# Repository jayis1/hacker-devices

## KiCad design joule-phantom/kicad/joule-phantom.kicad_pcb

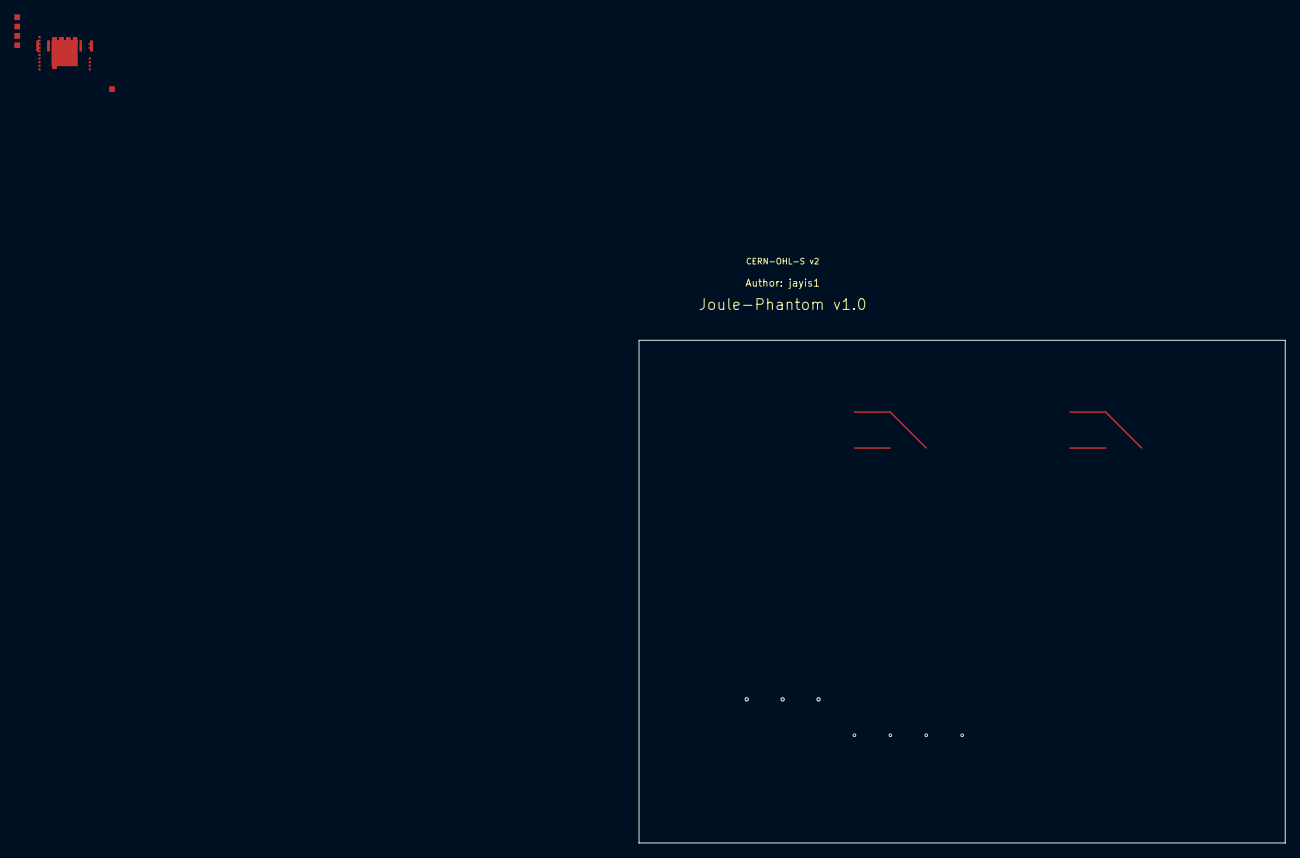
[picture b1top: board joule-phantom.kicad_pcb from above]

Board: 4 copper layers, 90.0 x 70.0 mm, 16 parts (0 on the bottom side), 12 nets.

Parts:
C1, C2: 100nF; C_0402_1005Metric
C3: 10uF; C_0603_1608Metric
D1: Blue; LED_0603_1608Metric
J1: Host_SMBus_6pin; TE_84953-6
J2: Batt_SMBus_6pin; TE_84953-6
R1, R2, R3, R4: 10k; R_0402_1005Metric
R5: 470; R_0402_1005Metric
U1: STM32L432KCU6; QFN-32-1EP_5x5mm_P0.5mm_EP3.65x3.65mm
U2: ESP32-C3-MINI-1
U3, U4: TXS0102DCT; SOT-23-8
Y1: 32.768kHz; Crystal_SMD_3215-2Pin_3.2x1.5mm

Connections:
3V3: C1.1, C2.1, C3.1, R1.1, R2.1, R3.1, R4.1, U1.1, U1.29, U2.1, U2.2, U3.1, U4.1
BATT_PRSNT#: J1.6, J2.6, U1.2
GND: C1.2, C2.2, C3.2, D1.1, J1.4, J2.4, R5.2, U1.10, U1.30, U1.33, U2.15, U3.4, U4.4
LED_DRIVE: D1.2, R5.1, U1.23
SMBALERT#: J1.5, J2.5, U1.3
SMB_CLK_BATT: J2.2, R3.2, U1.21, U4.2
SMB_CLK_HOST: J1.2, R1.2, U1.8, U3.2
SMB_DAT_BATT: J2.3, R4.2, U1.22, U4.3
SMB_DAT_HOST: J1.3, R2.2, U1.9, U3.3
UART_RX: U1.5, U2.3
UART_TX: U1.4, U2.4
VBAT+: J1.1, J2.1, U3.8, U4.8

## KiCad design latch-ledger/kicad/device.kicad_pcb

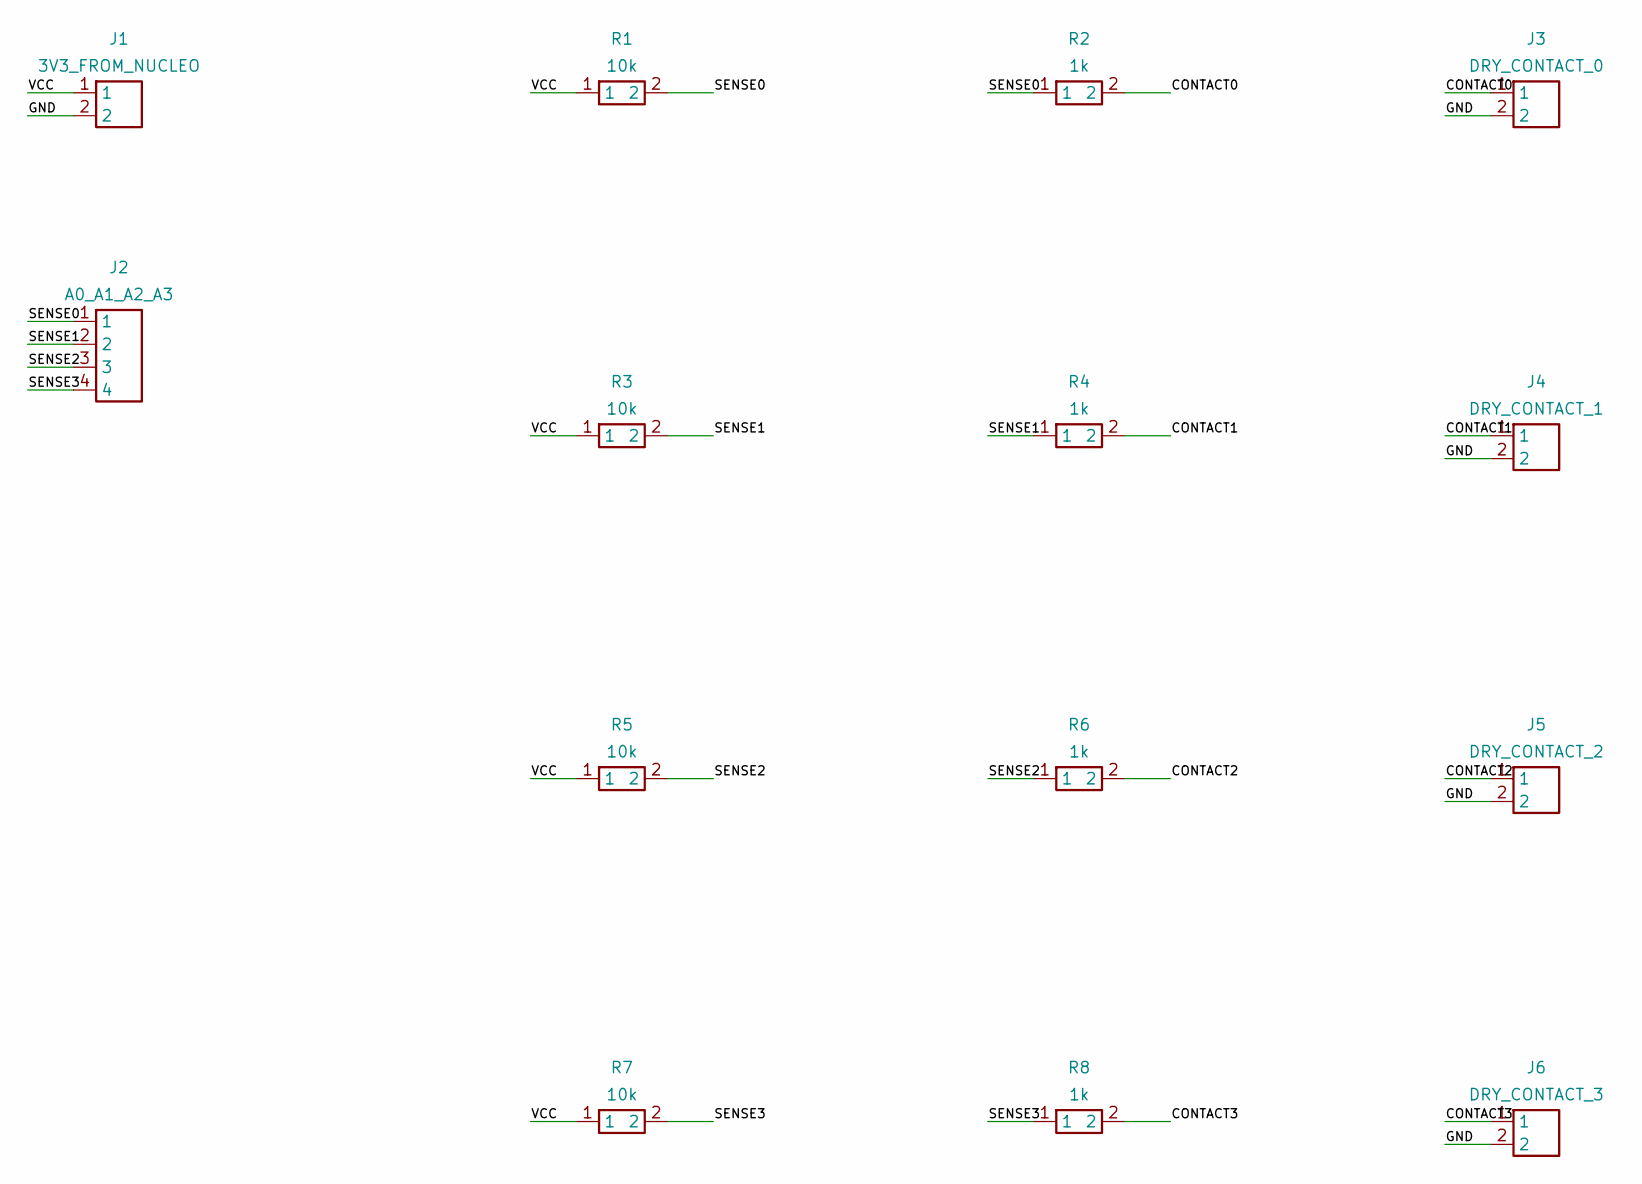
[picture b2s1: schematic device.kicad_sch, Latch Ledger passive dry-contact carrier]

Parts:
J1: 3V3_FROM_NUCLEO; PinHeader_1x02_P2.54mm_Vertical
J2: A0_A1_A2_A3; PinHeader_1x04_P2.54mm_Vertical
J3: DRY_CONTACT_0; PinHeader_1x02_P2.54mm_Vertical
J4: DRY_CONTACT_1; PinHeader_1x02_P2.54mm_Vertical
J5: DRY_CONTACT_2; PinHeader_1x02_P2.54mm_Vertical
J6: DRY_CONTACT_3; PinHeader_1x02_P2.54mm_Vertical
R1, R3, R5, R7: 10k; R_Axial_DIN0207_L6.3mm_D2.5mm_P7.62mm_Horizontal
R2, R4, R6, R8: 1k; R_Axial_DIN0207_L6.3mm_D2.5mm_P7.62mm_Horizontal

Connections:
CONTACT0: J3.1, R2.2
CONTACT1: J4.1, R4.2
CONTACT2: J5.1, R6.2
CONTACT3: J6.1, R8.2
GND: J1.2, J3.2, J4.2, J5.2, J6.2
SENSE0: J2.1, R1.2, R2.1
SENSE1: J2.2, R3.2, R4.1
SENSE2: J2.3, R5.2, R6.1
SENSE3: J2.4, R7.2, R8.1
VCC: J1.1, R1.1, R3.1, R5.1, R7.1

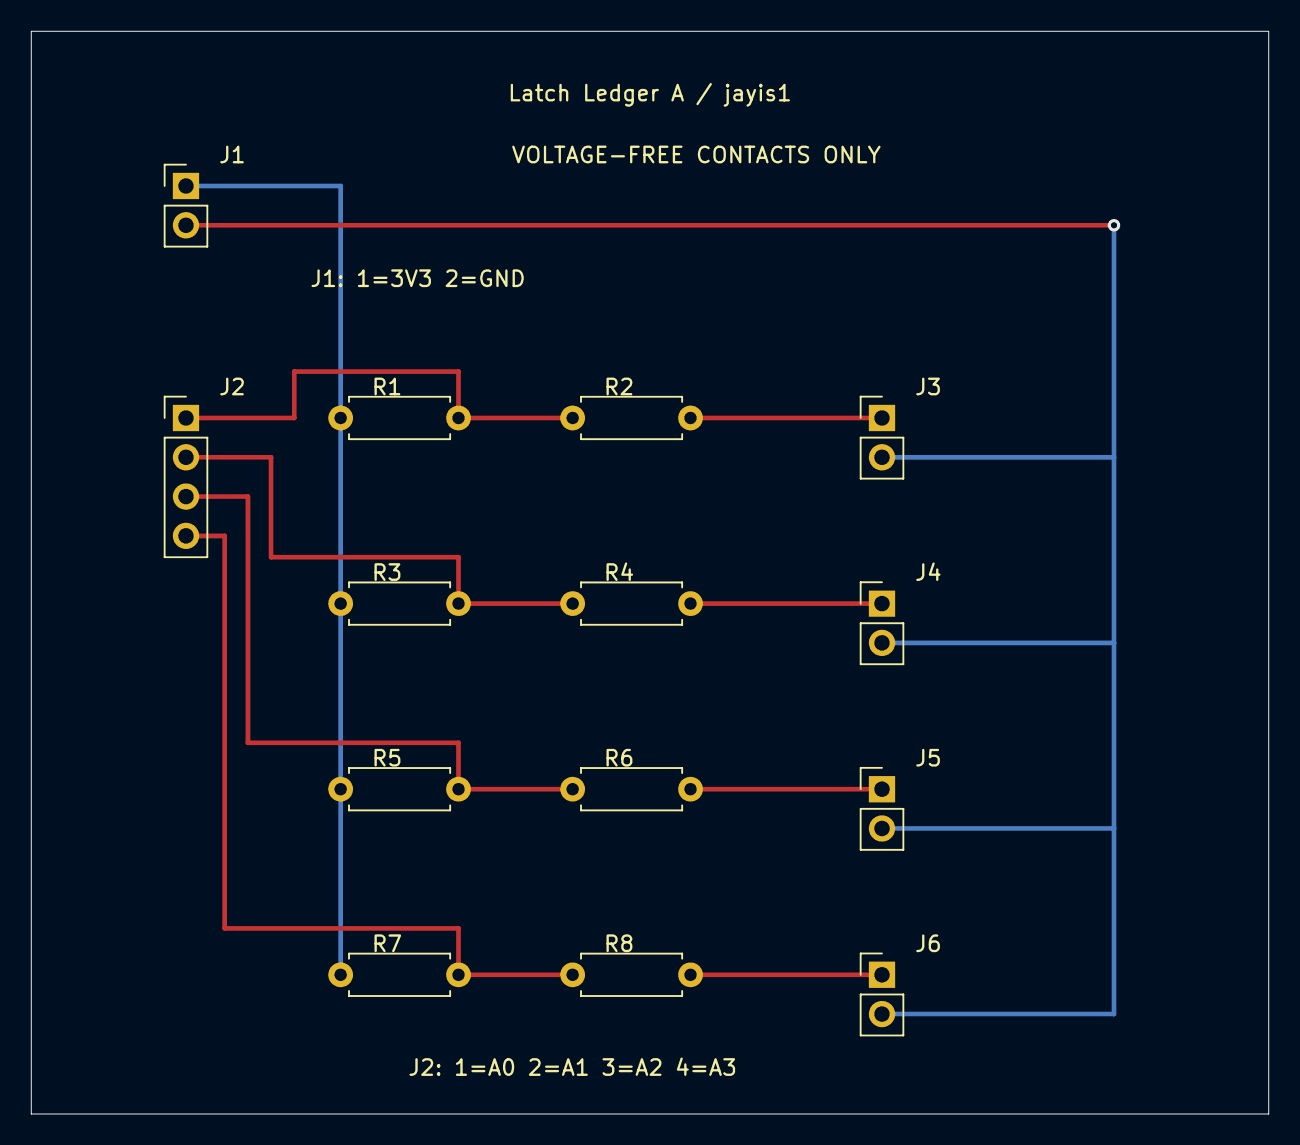
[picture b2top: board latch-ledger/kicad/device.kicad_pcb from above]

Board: 2 copper layers, 80.0 x 70.0 mm, 14 parts (0 on the bottom side), 10 nets.

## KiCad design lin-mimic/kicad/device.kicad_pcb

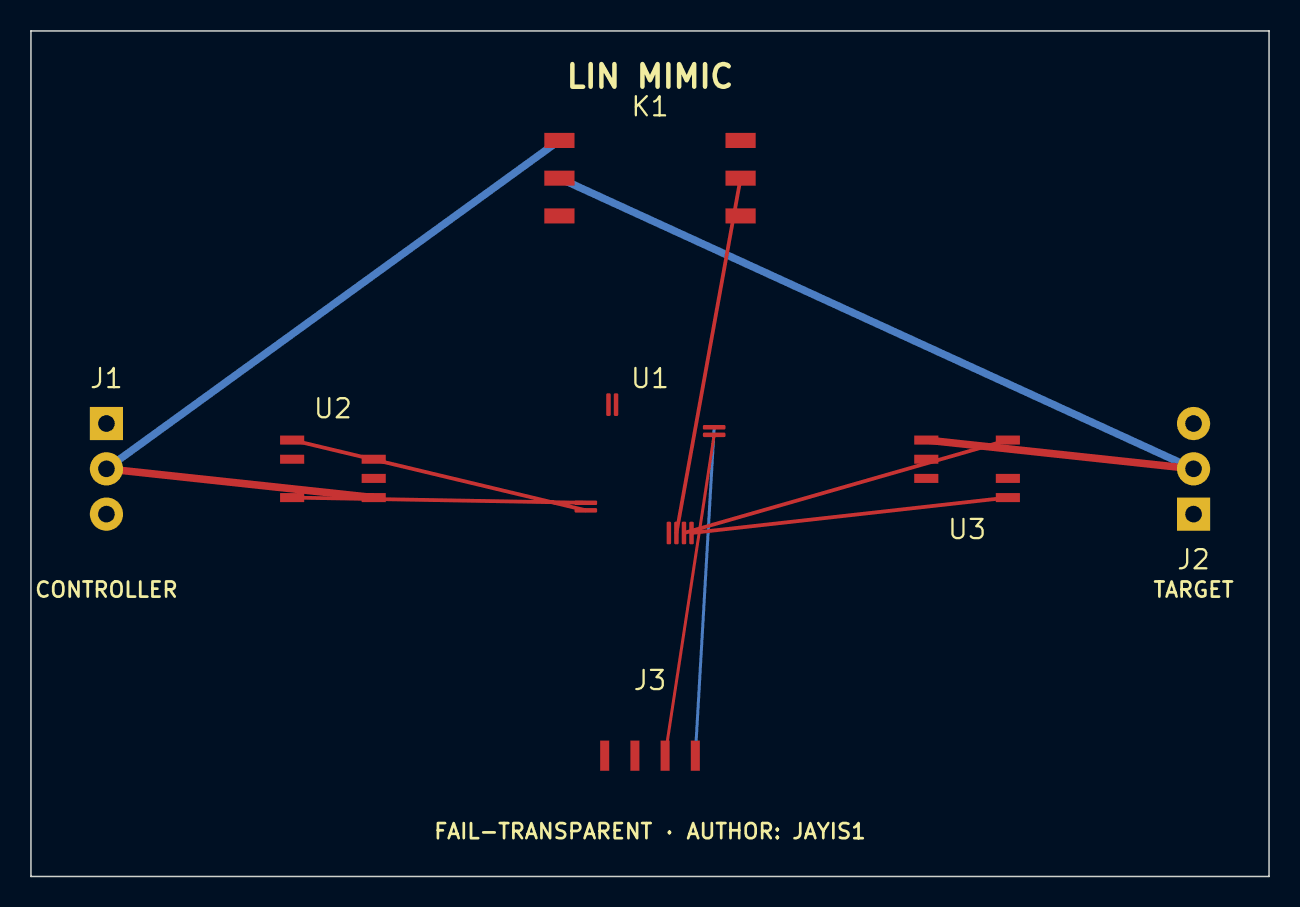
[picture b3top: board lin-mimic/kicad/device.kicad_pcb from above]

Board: 4 copper layers, 82.0 x 56.0 mm, 7 parts (0 on the bottom side), 12 nets.

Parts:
J1: CONTROLLER; Molex_Micro-Fit_3.0_43650-0300_1x03_P3.00mm_Horizontal
J2: TARGET; Molex_Micro-Fit_3.0_43650-0300_1x03_P3.00mm_Horizontal
J3: USB-C; USB_C_Receptacle_GCT_USB4105-xx-A_16P_TopMnt_Horizontal
K1: TQ2SA-L2-5V; Relay_DPDT_Panasonic_TQ2SA
U1: STM32G474CBT6; LQFP-48_7x7mm_P0.5mm
U2: TJA1021 CONTROLLER; SOIC-8_3.9x4.9mm_P1.27mm
U3: TJA1021 TARGET; SOIC-8_3.9x4.9mm_P1.27mm

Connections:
+3V3: U1.48, U2.8, U3.8
GND: J1.3, J2.3, J3.A1, K1.3, K1.4, U1.24, U1.47, U2.2, U3.2
LIN_CONTROLLER: J1.2, K1.1, U2.6
LIN_TARGET: J2.2, K1.2, U3.6
RELAY_DRIVE: K1.5, U1.23
USART2_RX: U1.13, U2.4
USART2_TX: U1.12, U2.1
USART3_RX: U1.22, U3.4
USART3_TX: U1.21, U3.1
USB_DM: J3.A7, U1.36
USB_DP: J3.A6, U1.35
VBAT_PROTECTED: J1.1, J2.1, J3.A4, K1.6, U2.7, U3.7

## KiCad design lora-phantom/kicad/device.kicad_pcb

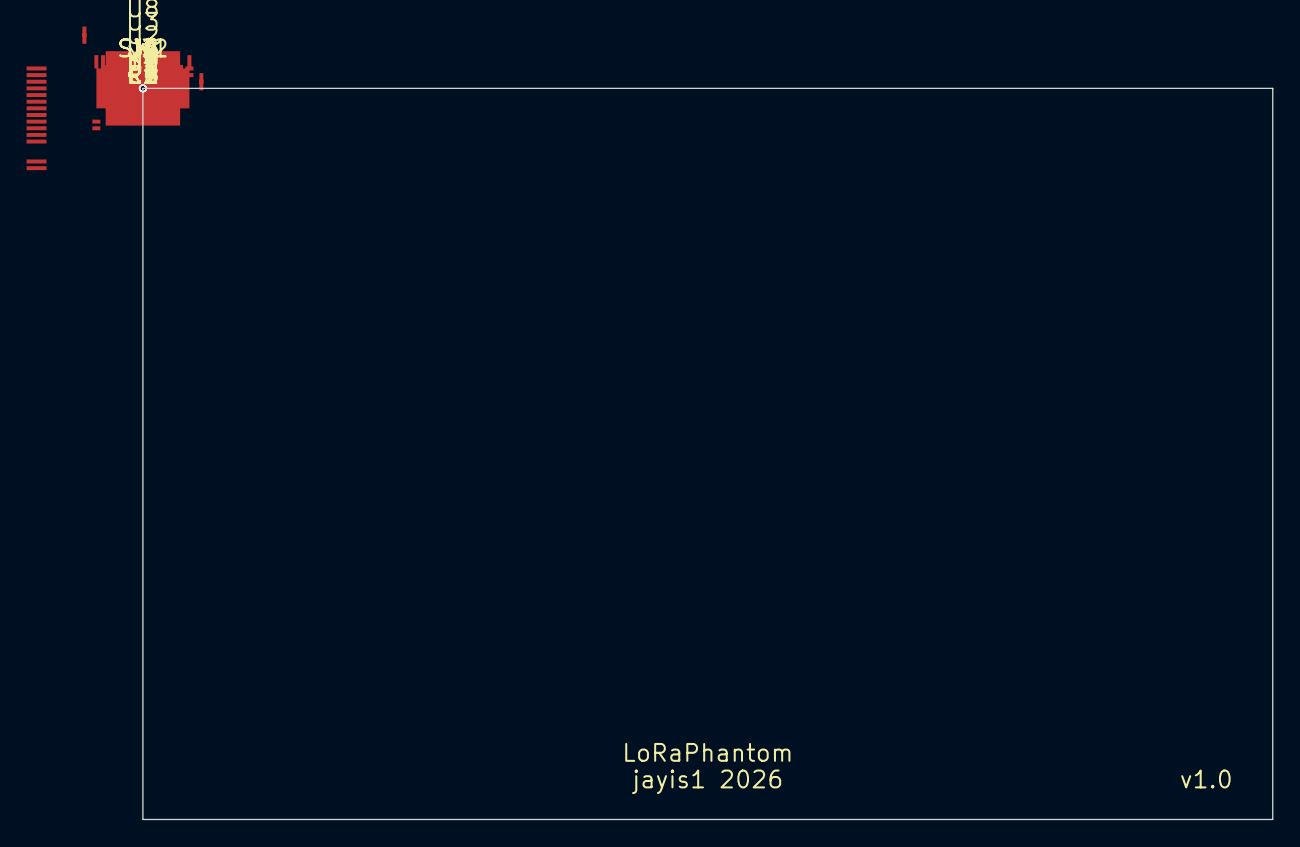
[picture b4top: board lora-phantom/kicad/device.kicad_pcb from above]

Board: 4 copper layers, 85.0 x 55.0 mm, 29 parts (0 on the bottom side), 17 nets.

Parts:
C1, C2, C4: 100nF; C_0402_1005Metric
C3, C5: 10uF; C_0402_1005Metric
D1: RF; LED_0603_1608Metric
D2: BLE; LED_0603_1608Metric
D3: USB; LED_0603_1608Metric
D4: ERR; LED_0603_1608Metric
J1: USB-C; USB_C_Receptacle_Amphenol_12401548E4-2A
J2: Micro_SD; microSD_HC_Hirose_DM3D-SF
J3: SMA; SMA_Amphenol_132289_EdgeMount
J4: BAT; JST_PH_S2B-PH-SM4-TB_1x02-1MP_P2.00mm
L1: 12nH; L_0402_1005Metric
R1: 1k; R_0402_1005Metric
R5: 100k; R_0402_1005Metric
R6: 200k; R_0402_1005Metric
SW1: CAPTURE; SW_Push_SPST_B3SN-6x6mm
SW2: MODE; SW_Push_SPST_B3SN-6x6mm
U1: STM32H743VIT6; LQFP-100_14x14mm_P0.5mm
U2: SX1262IMLTRT; QFN-24-1EP_4x4mm_P0.5mm_EP2.6x2.6mm
U3: nRF52840-QIAA-R; QFN-73-1EP_7x7mm_P0.5mm_EP5.6x5.6mm
U4: SKY66122-11; QFN-16-1EP_3x3mm_P0.5mm_EP1.8x1.8mm
U6: TPS63020DSJR; VQFN-14-1EP_3x3mm_P0.5mm_EP2x2mm
U7: MCP73831T-2ACI; SOT-23
U8: IS42S16160G-6TLI; TSOP-54_8.9x18.4mm_P0.5mm
U9: USBLC6-2SC6; SOT-23-6
Y1: 25MHz; Crystal_SMD_3225-4Pin_3.2x2.5mm
Y2: 32MHz TCXO; Oscillator_SMD_EuroQuartz_XO53-4Pin_5.0x3.2mm

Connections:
+3V3: C1.1, C2.1, C3.1, C4.1, C5.1, D1.1, D2.1, D3.1, D4.1, J2.4, U1.1, U2.1, U3.1, U4.1, U6.10, U8.1, Y2.4
+BATT: J4.1, R5.1, U6.1, U7.3
BAT_ADC: R5.2, R6.1
GND: C1.2, C2.2, C3.2, C4.2, C5.2, J1.B12, J2.3, J2.7, J3.2, J4.2, R1.2, R6.2, SW1.1, SW2.1, U1.2, U2.0, U2.2, U3.0, U3.2, U4.0, U6.0, U7.2, U8.2, U9.2, Y1.2, Y1.4, Y2.2
LED_RF: D1.2, R1.1, U7.5
RFIN: L1.2, U4.4
RFIO: L1.1, U2.13
SPI6_MISO: U1.7, U2.9
SPI6_MOSI: U1.8, U2.8
SPI6_NSS: U1.5, U2.7
SPI6_SCK: U1.6, U2.10
SX_RESET: U1.9, U2.11
USART3_RX: U1.13, U3.46
USART3_TX: U1.12, U3.45
USB_DM: J1.B7, U1.15, U9.1
USB_DP: J1.B6, U1.16, U9.6
VBUS: J1.A4, U7.1, U9.5

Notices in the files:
infrared-phantom/kicad/device.kicad_sch:
CERN-OHL-S v2
joule-phantom/kicad/joule-phantom.kicad_pcb:
License: CERN-OHL-S v2
lora-phantom/kicad/device.kicad_sch:
Author: jayis1 — License: CERN-OHL-S v2
